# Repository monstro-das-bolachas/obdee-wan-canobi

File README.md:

# OBDee-Wan CANobi

> Open-hardware automotive bus interface for CAN FD, classic CAN, LIN, and K-line exploration.

OBDee-Wan CANobi is a Teensy 4.1 based vehicle-network tool for hackers, makers, reverse engineers, EV converters, and curious learners who want hardware they can inspect and understand.

It is designed as a practical bridge between a laptop and a vehicle or bench module: powerful enough for real CAN FD/LIN/K-line experiments, but documented as a teaching project rather than a black box.

## At a glance

| Area | Current R11 target |
| --- | --- |
| Host | Teensy 4.1 |
| CAN FD | 2 external CAN FD controller paths |
| Transceivers | Dual CAN FD transceivers |
| Other buses | LIN / K-line support path |
| Vehicle connection | OBD pigtail-friendly wiring, not a direct-plug dongle |
| Configuration | DIP-switch selectable routing options |
| CAD | KiCad hardware source and generated fabrication packages |
| Readiness | Bare-PCB prototype candidate for bench bring-up |

## What you can use it for

- CAN FD experimentation and learning
- Classic CAN diagnostics and reverse engineering
- LIN and K-line bench experiments
- EV conversion support tooling
- Custom diagnostic interface development
- Teaching automotive networks with inspectable hardware
- Bench testing ECUs, modules, sensors, and harness fragments

## Current status: R11 prototype manufacturing candidate

R11 may be ordered as a small bare-PCB prototype batch for bench bring-up.

It is not approved for direct vehicle testing yet.

### Active release package

`revisions/00_WORK_R11_TRUE_DUAL_CANFD/release/R11_PROTOTYPE_MANUFACTURING_CANDIDATE_20260630/`

### Manufacturer upload ZIP

`revisions/00_WORK_R11_TRUE_DUAL_CANFD/release/R11_PROTOTYPE_MANUFACTURING_CANDIDATE_20260630/package/JLCPCB_PCBWAY_UPLOAD_R11_MINIMAL_GERBERS_ONLY_20260630.zip`

SHA256:

`434dedf475bb3443f1ffa6384541426fcef9cf96a792c1744b9c1bb7ff68faa8`

### Verification summary

| Check | Result |
| --- | --- |
| KiCad CLI PCB DRC | 0 violations |
| KiCad schematic catalog ERC | 0 errors / 0 warnings |
| Footprint errors | 0 |
| Known residual | 1 GND zone-to-zone report at 1.0000 mm / 1.0000 mm |
| Gerber/drill export | Successful |
| GND continuity | Visually confirmed in KiCad after refill/highlight |
| BOM/CPL | PCB-derived BOM, grouped BOM, JLCPCB draft BOM/CPL included |
| Vehicle-use approval | Not yet; bench validation required first |

The remaining GND item is a reviewed KiCad zone-report artifact for prototype PCB ordering. It is not a blanket safety approval for vehicle connection.

## Safety first

Vehicle electrical systems can damage tools, modules, or the car if connected incorrectly. Treat every first assembly as experimental hardware.

Before connecting to a vehicle:

1. Inspect the bare PCB.
2. Check for rail shorts with a multimeter.
3. Assemble and test the power section first.
4. Power up from a current-limited bench supply.
5. Verify OBD/pigtail pin mapping manually.
6. Confirm DIP-switch defaults and intended routing.
7. Test CAN/LIN/K behavior on bench modules first.
8. Use fusing and current limiting for any later vehicle test.

## Repository map

| Path | Purpose |
| --- | --- |
| `README_START_HERE.txt` | Short navigation and safety guide |
| `CURRENT_STATUS.md` | Current revision status, ordering notes, and verification summary |
| `revisions/00_WORK_R11_TRUE_DUAL_CANFD/` | Active R11 prototype candidate source and release package |
| `revisions/00_WORK_R11_TRUE_DUAL_CANFD/docs/R11_BOM_FROM_PCB.md` | PCB-derived R11 BOM and procurement-review starting point |
| `revisions/00_WORK_R11_TRUE_DUAL_CANFD/docs/R11_PCB_DERIVED_NETLIST.md` | Pad/net evidence exported from the active PCB |
| `LOCAL_ARCHIVE_POINTERS.md` | Local-only pointers to R2-R10 evolution archives on this machine |
| GitHub releases / tags | Previous R10 and R9 snapshots; not duplicated in the latest working tree |
| `LICENSE` | Main hardware license: CERN-OHL-P-2.0 |
| `LICENSES/` | Full license texts and license split documentation |

## Recommended first order

For the first prototype batch, use conservative bare-board settings:

| Option | Recommendation |
| --- | --- |
| Quantity | 5 or smallest economical batch |
| Layers | 2 |
| Material | FR-4 |
| Thickness | 1.6 mm |
| Copper | 1 oz |
| Surface finish | Standard low-cost prototype finish is acceptable |
| Electrical test | Yes |
| Assembly | No; hand-assemble and validate first |

## Naming note

The project name is a small joke:

OBDee-Wan CANobi: an OBD/CAN interface that helps you feel disturbances in the bus.

## License

This project is open source and open hardware.

| Content | License |
| --- | --- |
| Hardware design files, KiCad sources, PCB/manufacturing files | CERN-OHL-P-2.0 |
| Firmware, scripts, and software | MIT |
| Documentation | CC-BY-4.0 |

You are free to study, modify, build, remix, and share this project. Attribution is required where applicable: please credit the original project and author when reusing or publishing derivative work.

See `LICENSES/README.md` for the full license split and SPDX identifiers.

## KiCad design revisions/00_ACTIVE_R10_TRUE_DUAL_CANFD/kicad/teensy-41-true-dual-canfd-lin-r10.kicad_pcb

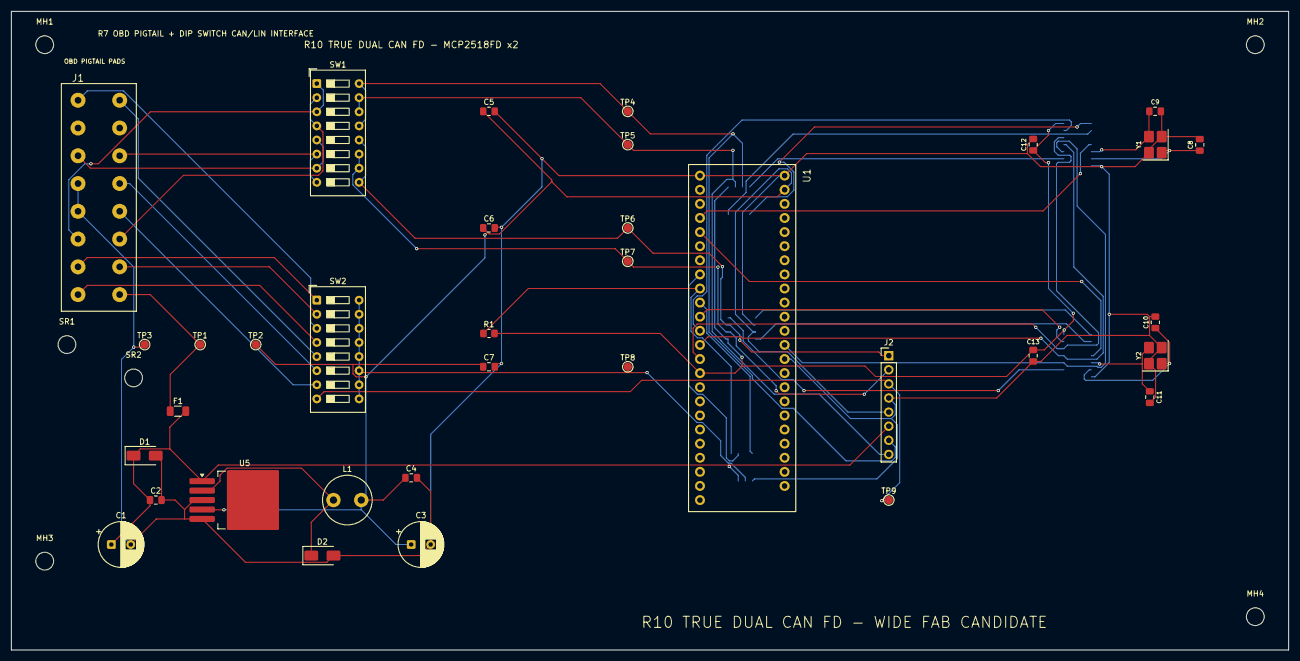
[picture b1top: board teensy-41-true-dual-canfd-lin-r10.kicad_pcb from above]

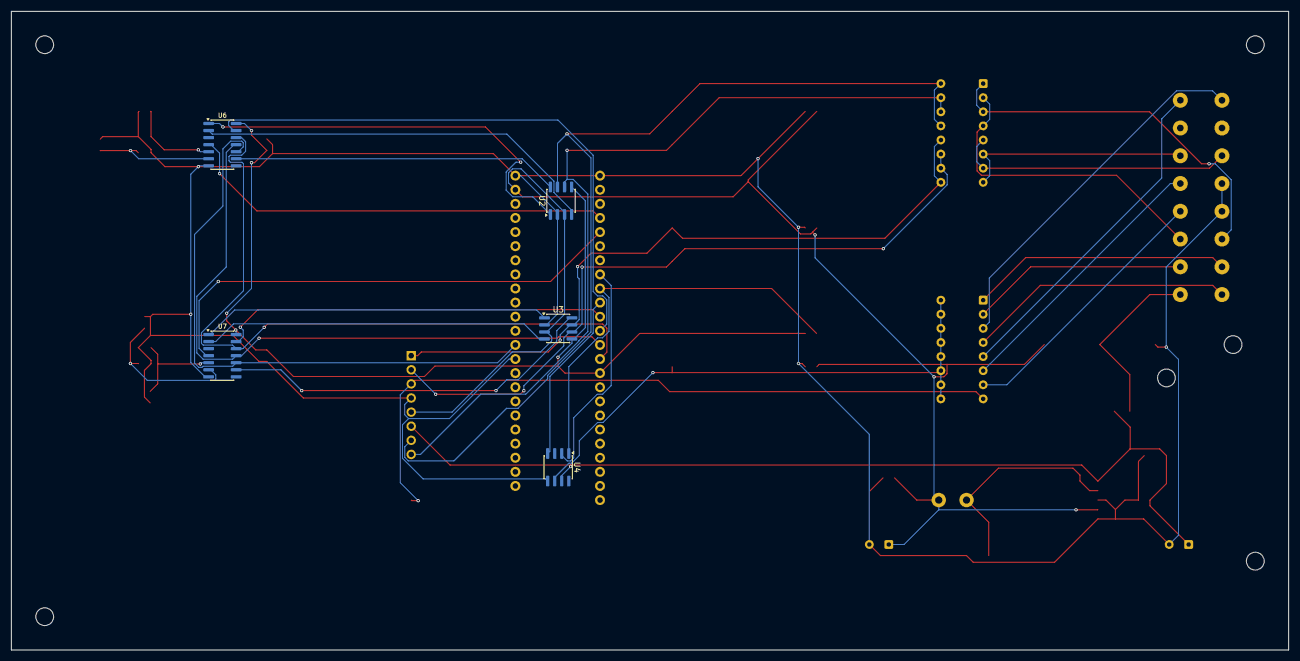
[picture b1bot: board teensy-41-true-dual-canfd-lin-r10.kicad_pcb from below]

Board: 2 copper layers, 230.0 x 115.0 mm, 46 parts (5 on the bottom side), 43 nets.

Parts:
C1: 100uF_50V_INPUT; CP_Radial_D8.0mm_P3.50mm
C2: 100nF_50V_INPUT; C_0805_2012Metric_Pad1.18x1.45mm_HandSolder
C3: 330uF_16V_OUTPUT_LOW_ESR; CP_Radial_D8.0mm_P3.50mm
C4: 100nF_16V_OUTPUT; C_0805_2012Metric_Pad1.18x1.45mm_HandSolder
C5: 100nF_CAN_A_DECOUPLING; C_0805_2012Metric_Pad1.18x1.45mm_HandSolder
C6: 100nF_CAN_B_DECOUPLING; C_0805_2012Metric_Pad1.18x1.45mm_HandSolder
C7: 100nF_LIN_DECOUPLING; C_0805_2012Metric_Pad1.18x1.45mm_HandSolder
C8: 22pF_Y1_OSC1; C_0805_2012Metric_Pad1.18x1.45mm_HandSolder
C9: 22pF_Y1_OSC2; C_0805_2012Metric_Pad1.18x1.45mm_HandSolder
C10: 22pF_Y2_OSC1; C_0805_2012Metric_Pad1.18x1.45mm_HandSolder
C11: 22pF_Y2_OSC2; C_0805_2012Metric_Pad1.18x1.45mm_HandSolder
C12: 100nF_U6_VDD; C_0805_2012Metric_Pad1.18x1.45mm_HandSolder
C13: 100nF_U7_VDD; C_0805_2012Metric_Pad1.18x1.45mm_HandSolder
D1: SMBJ24CA_TVS_12V; D_SMA
D2: SS34_BUCK_SCHOTTKY; D_SMA
F1: POLYFUSE_500mA; Fuse_1206_3216Metric
J1: OBD2_PIGTAIL_16_WIRE_SOLDER_PADS; OBD2_PigtailPads_Manufacturing
J2: AUX_HEADER; PinHeader_1x08_P2.54mm_Vertical
L1: 33uH_3A_BUCK_INDUCTOR; L_Radial_D8.7mm_P5.00mm_Fastron_07HCP
MH1, MH2, MH3, MH4: M3; MountingHole_3.2mm_M3
R1: 10k_LIN_RX_PULLUP; R_0805_2012Metric_Pad1.20x1.40mm_HandSolder
SR1, SR2: CABLE_STRAIN_RELIEF; MountingHole_3.2mm_M3
SW1: CAN_NORMAL_CROSS_DIP_8POS; SW_DIP_SPSTx08_Slide_9.78x22.5mm_W7.62mm_P2.54mm
SW2: LIN_K_SOURCE_DIP_8POS_SELECT_ONE; SW_DIP_SPSTx08_Slide_9.78x22.5mm_W7.62mm_P2.54mm
TP1: 12V; TestPoint_Pad_D1.5mm
TP2: 5V; TestPoint_Pad_D1.5mm
TP3: GND; TestPoint_Pad_D1.5mm
TP4: CAN_A_H; TestPoint_Pad_D1.5mm
TP5: CAN_A_L; TestPoint_Pad_D1.5mm
TP6: CAN_B_H; TestPoint_Pad_D1.5mm
TP7: CAN_B_L; TestPoint_Pad_D1.5mm
TP8: LIN_BUS; TestPoint_Pad_D1.5mm
TP9: AUX_LIN_K; TestPoint_Pad_D1.5mm
U1: TEENSY_4.1_MAIN_HEADERS_PJRC_AUDITED; Teensy_4.1_MainHeaders_PJRC_Audited
U2: MCP2562FD_CAN_A_3V3_IO; SOIC-8_3.9x4.9mm_P1.27mm
U3: MCP2562FD_CAN_B_3V3_IO; SOIC-8_3.9x4.9mm_P1.27mm
U4: TLIN1029DRQ1_LIN_3V3_LOGIC; SOIC-8_3.9x4.9mm_P1.27mm
U5: LM2596S-5.0_BUCK; TO-263-5_TabPin3
U6: MCP2518FD_A_SOIC14; SOIC-14_3.9x8.7mm_P1.27mm
U7: MCP2518FD_B_SOIC14; SOIC-14_3.9x8.7mm_P1.27mm
Y1, Y2: 40MHz_3225_VERIFY_CL; Crystal_SMD_3225-4Pin_3.2x2.5mm_HandSoldering

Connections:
+3V3: C12.1, C13.1, R1.2, U1.3V3_B, U2.5, U3.5, U6.14, U7.14
+5V_REGULATED: C3.1, C4.1, C5.1, C6.1, C7.1, J2.5, L1.2, TP2.1, U1.VIN, U2.3, U3.3, U5.4
+12V_OBD: F1.1, J1.16, TP1.1
+12V_PROTECTED: C1.1, C2.1, D1.1, F1.2, J2.6, U4.7, U5.1
AUX_LIN_K_IO: J2.3, SW2.8, TP9.1
BUCK_SW: D2.1, L1.1, U5.2
CANFD_A_INT: U1.2, U6.4
CANFD_A_NCS: U1.10, U6.13
CANFD_A_OSC1: C8.1, U6.6, Y1.1
CANFD_A_OSC2: C9.1, U6.5, Y1.3
CANFD_A_RXCAN: U2.4, U6.2
CANFD_A_TXCAN: U2.1, U6.1
CANFD_A_XSTBY: U2.8, U6.9
CANFD_B_INT: U1.3, U7.4
CANFD_B_NCS: U1.9, U7.13
CANFD_B_OSC1: C10.1, U7.6, Y2.1
CANFD_B_OSC2: C11.1, U7.5, Y2.3
CANFD_B_RXCAN: U3.4, U7.2
CANFD_B_TXCAN: U3.1, U7.1
CANFD_B_XSTBY: U3.8, U7.9
CANFD_SPI_SCK: U1.13, U6.10, U7.10
CANFD_SPI_SDI_MOSI: U1.11, U6.11, U7.11
CANFD_SPI_SDO_MISO: U1.12, U6.12, U7.12
CAN_A_H: J2.7, SW1.13, SW1.16, TP4.1, U2.7
CAN_A_L: J2.8, SW1.14, SW1.15, TP5.1, U2.6
CAN_B_H: J2.1, SW1.9, SW1.12, TP6.1, U3.7
CAN_B_L: J2.2, SW1.10, SW1.11, TP7.1, U3.6
GND: C1.2, C2.2, C3.2, C4.2, C5.2, C6.2, C7.2, C8.2, C9.2, C10.2, C11.2, C12.2, C13.2, D1.2, D2.2, J1.4, J1.5, J2.4, TP3.1, U1.GND_B1, U1.GND_T1, U1.GND_T2, U2.2, U3.2, U4.5, U5.3, U5.5, U6.7, U7.7, Y1.2, Y1.4, Y2.2, Y2.4
LIN_BUS: SW2.9, SW2.10, SW2.11, SW2.12, SW2.13, SW2.14, SW2.15, SW2.16, TP8.1, U4.6
LIN_EN: U1.6, U4.2
LIN_RX: R1.1, U1.7, U4.1
LIN_TX: U1.8, U4.4
OBD1_SINGLE_WIRE_CANDIDATE: J1.1, SW2.3
OBD3_CAN_B_PAIR_A_CANDIDATE: J1.3, SW1.5, SW1.7
OBD6_CAN_A_PAIR_A: J1.6, SW1.1, SW1.3
OBD7_SINGLE_WIRE_CANDIDATE: J1.7, SW2.1
OBD8_SINGLE_WIRE_CANDIDATE: J1.8, SW2.4
OBD9_SINGLE_WIRE_CANDIDATE: J1.9, SW2.5
OBD11_CAN_B_PAIR_B_CANDIDATE: J1.11, SW1.6, SW1.8
OBD12_SINGLE_WIRE_CANDIDATE: J1.12, SW2.6
OBD13_SINGLE_WIRE_CANDIDATE: J1.13, SW2.7
OBD14_CAN_A_PAIR_B: J1.14, SW1.2, SW1.4
OBD15_SINGLE_WIRE_CANDIDATE: J1.15, SW2.2

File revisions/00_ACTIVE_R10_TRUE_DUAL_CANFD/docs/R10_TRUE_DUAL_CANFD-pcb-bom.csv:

Reference,Value,Footprint,Layer,X_mm,Y_mm,Rotation_deg,DNP
C1,100uF_50V_INPUT,CP_Radial_D8.0mm_P3.50mm,F.Cu,18.000,96.000,0.00,no
C10,22pF_Y2_OSC1,C_0805_2012Metric_Pad1.18x1.45mm_HandSolder,F.Cu,206.000,56.000,90.00,no
C11,22pF_Y2_OSC2,C_0805_2012Metric_Pad1.18x1.45mm_HandSolder,F.Cu,205.000,69.463,-90.00,no
C12,100nF_U6_VDD,C_0805_2012Metric_Pad1.18x1.45mm_HandSolder,F.Cu,184.000,24.000,90.00,no
C13,100nF_U7_VDD,C_0805_2012Metric_Pad1.18x1.45mm_HandSolder,F.Cu,184.000,62.000,-90.00,no
C2,100nF_50V_INPUT,C_0805_2012Metric_Pad1.18x1.45mm_HandSolder,F.Cu,26.000,88.000,0.00,no
C3,330uF_16V_OUTPUT_LOW_ESR,CP_Radial_D8.0mm_P3.50mm,F.Cu,72.000,96.000,0.00,no
C4,100nF_16V_OUTPUT,C_0805_2012Metric_Pad1.18x1.45mm_HandSolder,F.Cu,72.000,84.000,0.00,no
C5,100nF_CAN_A_DECOUPLING,C_0805_2012Metric_Pad1.18x1.45mm_HandSolder,F.Cu,86.000,18.000,0.00,no
C6,100nF_CAN_B_DECOUPLING,C_0805_2012Metric_Pad1.18x1.45mm_HandSolder,F.Cu,86.000,39.000,0.00,no
C7,100nF_LIN_DECOUPLING,C_0805_2012Metric_Pad1.18x1.45mm_HandSolder,F.Cu,86.000,64.000,0.00,no
C8,22pF_Y1_OSC1,C_0805_2012Metric_Pad1.18x1.45mm_HandSolder,F.Cu,214.000,24.038,90.00,no
C9,22pF_Y1_OSC2,C_0805_2012Metric_Pad1.18x1.45mm_HandSolder,F.Cu,205.963,18.000,0.00,no
D1,SMBJ24CA_TVS_12V,D_SMA,F.Cu,24.000,80.000,0.00,no
D2,SS34_BUCK_SCHOTTKY,D_SMA,F.Cu,56.000,98.000,0.00,no
F1,POLYFUSE_500mA,Fuse_1206_3216Metric,F.Cu,30.000,72.000,0.00,no
J1,OBD2_PIGTAIL_16_WIRE_SOLDER_PADS,OBD2_PigtailPads_Manufacturing,F.Cu,0.000,0.000,0.00,no
J2,AUX_HEADER,PinHeader_1x08_P2.54mm_Vertical,F.Cu,158.000,62.000,0.00,no
L1,33uH_3A_BUCK_INDUCTOR,L_Radial_D8.7mm_P5.00mm_Fastron_07HCP,F.Cu,58.000,88.000,0.00,no
MH1,M3,MountingHole_3.2mm_M3,F.Cu,6.000,6.000,0.00,no
MH2,M3,MountingHole_3.2mm_M3,F.Cu,224.000,6.000,0.00,no
MH3,M3,MountingHole_3.2mm_M3,F.Cu,6.000,99.000,0.00,no
MH4,M3,MountingHole_3.2mm_M3,F.Cu,224.000,109.000,0.00,no
R1,10k_LIN_RX_PULLUP,R_0805_2012Metric_Pad1.20x1.40mm_HandSolder,F.Cu,86.000,58.000,0.00,no
SR1,CABLE_STRAIN_RELIEF,MountingHole_3.2mm_M3,F.Cu,10.000,60.000,0.00,no
SR2,CABLE_STRAIN_RELIEF,MountingHole_3.2mm_M3,F.Cu,22.000,66.000,0.00,no
SW1,CAN_NORMAL_CROSS_DIP_8POS,SW_DIP_SPSTx08_Slide_9.78x22.5mm_W7.62mm_P2.54mm,F.Cu,55.000,13.000,0.00,no
SW2,LIN_K_SOURCE_DIP_8POS_SELECT_ONE,SW_DIP_SPSTx08_Slide_9.78x22.5mm_W7.62mm_P2.54mm,F.Cu,55.000,52.000,0.00,no
TP1,12V,TestPoint_Pad_D1.5mm,F.Cu,34.000,60.000,0.00,no
TP2,5V,TestPoint_Pad_D1.5mm,F.Cu,44.000,60.000,0.00,no
TP3,GND,TestPoint_Pad_D1.5mm,F.Cu,24.000,60.000,0.00,no
TP4,CAN_A_H,TestPoint_Pad_D1.5mm,F.Cu,111.000,18.000,0.00,no
TP5,CAN_A_L,TestPoint_Pad_D1.5mm,F.Cu,111.000,24.000,0.00,no
TP6,CAN_B_H,TestPoint_Pad_D1.5mm,F.Cu,111.000,39.000,0.00,no
TP7,CAN_B_L,TestPoint_Pad_D1.5mm,F.Cu,111.000,45.000,0.00,no
TP8,LIN_BUS,TestPoint_Pad_D1.5mm,F.Cu,111.000,64.000,0.00,no
TP9,AUX_LIN_K,TestPoint_Pad_D1.5mm,F.Cu,158.000,88.000,0.00,no
U1,TEENSY_4.1_MAIN_HEADERS_PJRC_AUDITED,Teensy_4.1_MainHeaders_PJRC_Audited,F.Cu,154.240,-88.420,-90.00,no
U2,MCP2562FD_CAN_A_3V3_IO,SOIC-8_3.9x4.9mm_P1.27mm,B.Cu,131.025,34.095,90.00,no
U3,MCP2562FD_CAN_B_3V3_IO,SOIC-8_3.9x4.9mm_P1.27mm,B.Cu,131.525,57.095,180.00,no
U4,TLIN1029DRQ1_LIN_3V3_LOGIC,SOIC-8_3.9x4.9mm_P1.27mm,B.Cu,131.525,82.095,-90.00,no
U5,LM2596S-5.0_BUCK,TO-263-5_TabPin3,F.Cu,42.000,88.000,0.00,no
U6,MCP2518FD_A_SOIC14,SOIC-14_3.9x8.7mm_P1.27mm,B.Cu,192.000,24.000,180.00,no
U7,MCP2518FD_B_SOIC14,SOIC-14_3.9x8.7mm_P1.27mm,B.Cu,192.000,62.000,180.00,no
Y1,40MHz_3225_VERIFY_CL,Crystal_SMD_3225-4Pin_3.2x2.5mm_HandSoldering,F.Cu,206.000,24.000,90.00,no
Y2,40MHz_3225_VERIFY_CL,Crystal_SMD_3225-4Pin_3.2x2.5mm_HandSoldering,F.Cu,206.000,62.000,90.00,no

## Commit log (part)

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2026-06-21 Add R7 Teensy footprint corrected candidate
2026-06-22 Add R9 FAB_READY hardware release
    Promote R9 as the active manufacturing prototype candidate. Include KiCad PCB source, project-local footprints, Gerber/drill outputs, DRC reports, clean FAB_READY package, and changelog.
2026-06-22 Organize public R9 hardware release
2026-06-30 Add R10 true dual CAN FD release
